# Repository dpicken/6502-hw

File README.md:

# 6502-hw

Schematics and PCBs for a [Ben Eater](https://eater.net/6502) inspired 6502 computer.

## SBC

The single board computer ([schematic](/pdf/sbc.pdf), [layout](pdf/sbc.pcb.pdf), [BOM](bom/sbc.md)), features include:

  - 65C02 CPU, 8 MHz (with a suitable EEPROM)
  - ATF22V10C PLD (address space decode and IRQ glue)
  - 32 KiB ROM
  - 32 KiB RAM
  - 32 GiB microSD mass storage
  - 3 VIAs (1 system, 2 user accessible)
  - USB serial

### Programmable Logic

Install [rust](https://www.rust-lang.org/tools/install), then install galette:

```
git clone https://github.com/simon-frankau/galette
bash -c "cd galette; cargo build --release"
cp galette/target/release/galette ~/bin
```

Clone the fab build system and the 6502-hw project:

```
git clone https://github.com/dpicken/fab
git clone https://github.com/dpicken/6502-hw
```

Build:

```
cd 6502-hw
make
```

Write ATF22v10C:

```
make install
```

### Software

- See [dpicken/6502-os](https://github.com/dpicken/6502-os).

## SBC Controller

A controller for the single board computer ([schematic](/pdf/sbc-exp-control.pdf), [layout](pdf/sbc-exp-control.pcb.pdf), [BOM](bom/sbc-exp-control.md)).

## SBC Display - 20x4 OLED character module

An OLED display for the single board computer ([schematic](/pdf/sbc-exp-nhd_0420cw-interposer.pdf), [layout](pdf/sbc-exp-nhd_0420cw-interposer.pcb.pdf), [BOM](bom/sbc-exp-nhd_0420cw-interposer.md)).

## SBC Display - 40x4 or 20x4 LCD character module

An LCD display for the single board computer ([schematic](/pdf/sbc-exp-erm4004_erm2004-interposer.pdf), [layout](pdf/sbc-exp-erm4004_erm2004-interposer.pcb.pdf), [BOM](bom/sbc-exp-erm4004_erm2004-interposer.md)).

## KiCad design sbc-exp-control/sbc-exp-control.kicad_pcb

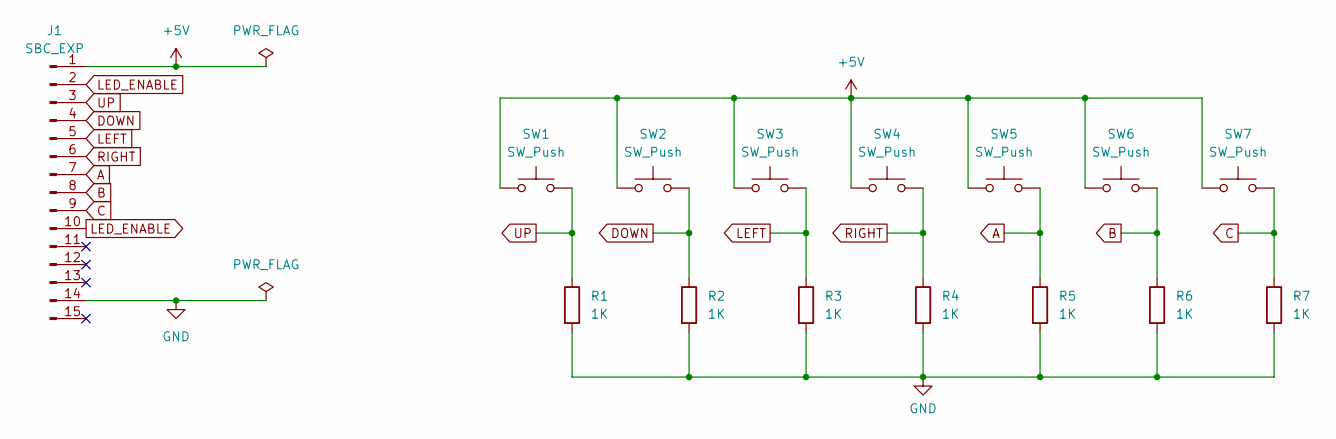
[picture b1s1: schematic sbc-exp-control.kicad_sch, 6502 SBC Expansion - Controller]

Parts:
J1: SBC_EXP; PinHeader_1x15_P2.54mm_Vertical
R1, R2, R3, R4, R5, R6, R7: 1K; R_0805_2012Metric_Pad1.20x1.40mm_HandSolder
SW1, SW2, SW3, SW4, SW5, SW6, SW7: SW_Push; SW_Push_1P1T_NO_6x6mm_H9.5mm

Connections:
+5V: J1.1, SW1.1, SW2.1, SW3.1, SW4.1, SW5.1, SW6.1, SW7.1
A: J1.7, R5.1, SW5.2
B: J1.8, R6.1, SW6.2
C: J1.9, R7.1, SW7.2
DOWN: J1.4, R2.1, SW2.2
GND: J1.14, R1.2, R2.2, R3.2, R4.2, R5.2, R6.2, R7.2
LED_ENABLE: J1.2, J1.10
LEFT: J1.5, R3.1, SW3.2
RIGHT: J1.6, R4.1, SW4.2
UP: J1.3, R1.1, SW1.2

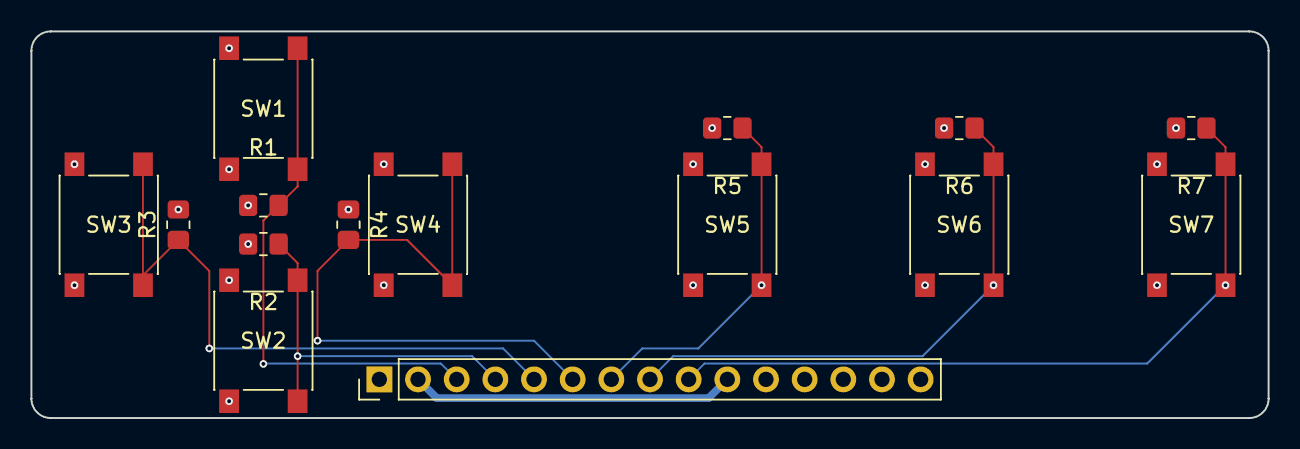
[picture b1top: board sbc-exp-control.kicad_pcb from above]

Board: 4 copper layers, 81.3 x 25.4 mm, 15 parts (0 on the bottom side), 10 nets.

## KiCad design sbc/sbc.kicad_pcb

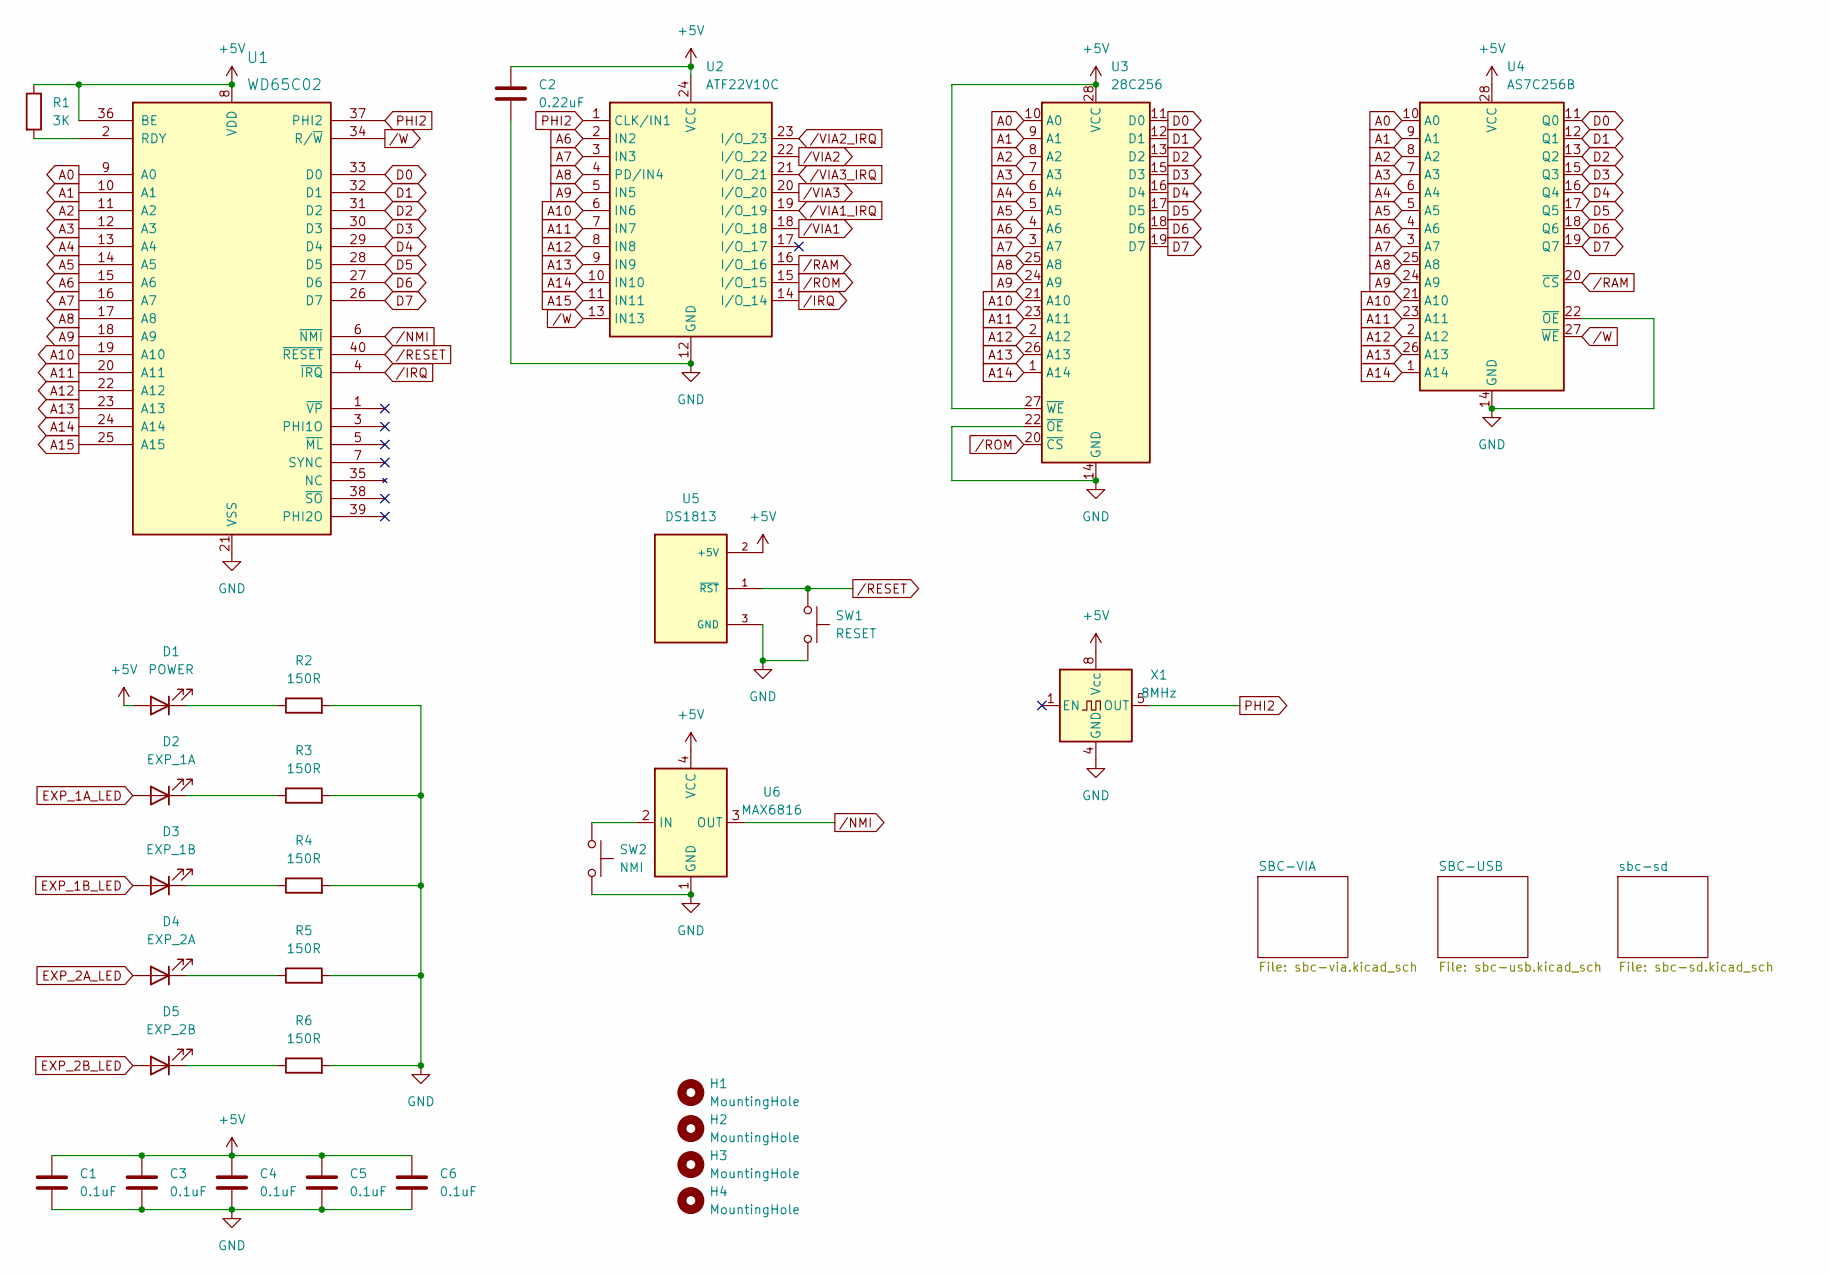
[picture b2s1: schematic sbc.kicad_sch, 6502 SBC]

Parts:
C1, C3, C4, C5, C6: 0.1uF; C_0805_2012Metric_Pad1.18x1.45mm_HandSolder
C2: 0.22uF; C_0805_2012Metric_Pad1.18x1.45mm_HandSolder
D1: POWER; LED_Rectangular_W5.0mm_H2.0mm
D2: EXP_1A; LED_Rectangular_W5.0mm_H2.0mm
D3: EXP_1B; LED_Rectangular_W5.0mm_H2.0mm
D4: EXP_2A; LED_Rectangular_W5.0mm_H2.0mm
D5: EXP_2B; LED_Rectangular_W5.0mm_H2.0mm
H1, H2, H3, H4: MountingHole; MountingHole_2.2mm_M2_Pad
R1: 3K; R_0805_2012Metric_Pad1.20x1.40mm_HandSolder
R2, R3, R4, R5, R6: 150R; R_0805_2012Metric_Pad1.20x1.40mm_HandSolder
SW1: RESET; SW_PUSH_6mm_H4.3mm
SW2: NMI; SW_PUSH_6mm_H4.3mm
U1: WD65C02; DIP-40_W15.24mm_Socket
U2: ATF22V10C; DIP-24_W7.62mm_Socket
U3: 28C256; DIP-28_W15.24mm_Socket
U4: AS7C256B; DIP-28_W7.62mm_Socket
U5: DS1813; SOT-23_Handsoldering
U6: MAX6816; SOT-143_Handsoldering
X1: 8MHz; Oscillator_DIP-8

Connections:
+5V: C1.1, C2.1, C3.1, C4.1, C5.1, C6.1, D1.2 (A), R1.1, U1.8 (VDD), U1.36 (BE), U2.24 (VCC), U3.27 (~WE), U3.28 (VCC), U4.28 (VCC), U5.2 (+5V), U6.4 (VCC), X1.8 (Vcc); also elsewhere on the board
A0: U1.9 (A0), U3.10 (A0), U4.10 (A0); also elsewhere on the board
A1: U1.10 (A1), U3.9 (A1), U4.9 (A1); also elsewhere on the board
A2: U1.11 (A2), U3.8 (A2), U4.8 (A2); also elsewhere on the board
A3: U1.12 (A3), U3.7 (A3), U4.7 (A3); also elsewhere on the board
A4: U1.13 (A4), U3.6 (A4), U4.6 (A4)
A5: U1.14 (A5), U3.5 (A5), U4.5 (A5)
A6: U1.15 (A6), U2.2 (IN2), U3.4 (A6), U4.4 (A6)
A7: U1.16 (A7), U2.3 (IN3), U3.3 (A7), U4.3 (A7)
A8: U1.17 (A8), U2.4 (PD/IN4), U3.25 (A8), U4.25 (A8)
A9: U1.18 (A9), U2.5 (IN5), U3.24 (A9), U4.24 (A9)
A10: U1.19 (A10), U2.6 (IN6), U3.21 (A10), U4.21 (A10)
A11: U1.20 (A11), U2.7 (IN7), U3.23 (A11), U4.23 (A11)
A12: U1.22 (A12), U2.8 (IN8), U3.2 (A12), U4.2 (A12)
A13: U1.23 (A13), U2.9 (IN9), U3.26 (A13), U4.26 (A13)
A14: U1.24 (A14), U2.10 (IN10), U3.1 (A14), U4.1 (A14)
A15: U1.25 (A15), U2.11 (IN11)
D0: U1.33 (D0), U3.11 (D0), U4.11 (Q0); also elsewhere on the board
D1: U1.32 (D1), U3.12 (D1), U4.12 (Q1); also elsewhere on the board
D2: U1.31 (D2), U3.13 (D2), U4.13 (Q2); also elsewhere on the board
D3: U1.30 (D3), U3.15 (D3), U4.15 (Q3); also elsewhere on the board
D4: U1.29 (D4), U3.16 (D4), U4.16 (Q4); also elsewhere on the board
D5: U1.28 (D5), U3.17 (D5), U4.17 (Q5); also elsewhere on the board
D6: U1.27 (D6), U3.18 (D6), U4.18 (Q6); also elsewhere on the board
D7: U1.26 (D7), U3.19 (D7), U4.19 (Q7); also elsewhere on the board
EXP_1A_LED: D2.2 (A); also elsewhere on the board
EXP_1B_LED: D3.2 (A); also elsewhere on the board
EXP_2A_LED: D4.2 (A); also elsewhere on the board
EXP_2B_LED: D5.2 (A); also elsewhere on the board
GND: C1.2, C2.2, C3.2, C4.2, C5.2, C6.2, R2.2, R3.2, R4.2, R5.2, R6.2, SW1.2, SW2.2, U1.21 (VSS), U2.12 (GND), U3.14 (GND), U3.22 (~OE), U4.14 (GND), U4.22 (~OE), U5.3 (GND), U6.1 (GND), X1.4 (GND); also elsewhere on the board
unnamed: D1.1 (K), R2.1
unnamed: D2.1 (K), R3.1
unnamed: D3.1 (K), R4.1
unnamed: D4.1 (K), R5.1
unnamed: D5.1 (K), R6.1
unnamed: R1.2, U1.2 (RDY)
unnamed: SW2.1, U6.2 (IN)
PHI2: U1.37 (PHI2), U2.1 (CLK/IN1), X1.5 (OUT); also elsewhere on the board
/IRQ: U1.4 (~IRQ), U2.14 (I/O_14)
/NMI: U1.6 (~NMI), U6.3 (OUT)
/RAM: U2.16 (I/O_16), U4.20 (~CS)
/RESET: SW1.1, U1.40 (~RESET), U5.1 (~RST); also elsewhere on the board
/ROM: U2.15 (I/O_15), U3.20 (~CS)
/VIA1: U2.18 (I/O_18); also elsewhere on the board
/VIA1_IRQ: U2.19 (I/O_19); also elsewhere on the board
/VIA2: U2.22 (I/O_22); also elsewhere on the board
/VIA2_IRQ: U2.23 (I/O_23); also elsewhere on the board
/VIA3: U2.20 (I/O_20); also elsewhere on the board
/VIA3_IRQ: U2.21 (I/O_21); also elsewhere on the board
/W: U1.34 (R/~W), U2.13 (IN13), U4.27 (~WE); also elsewhere on the board

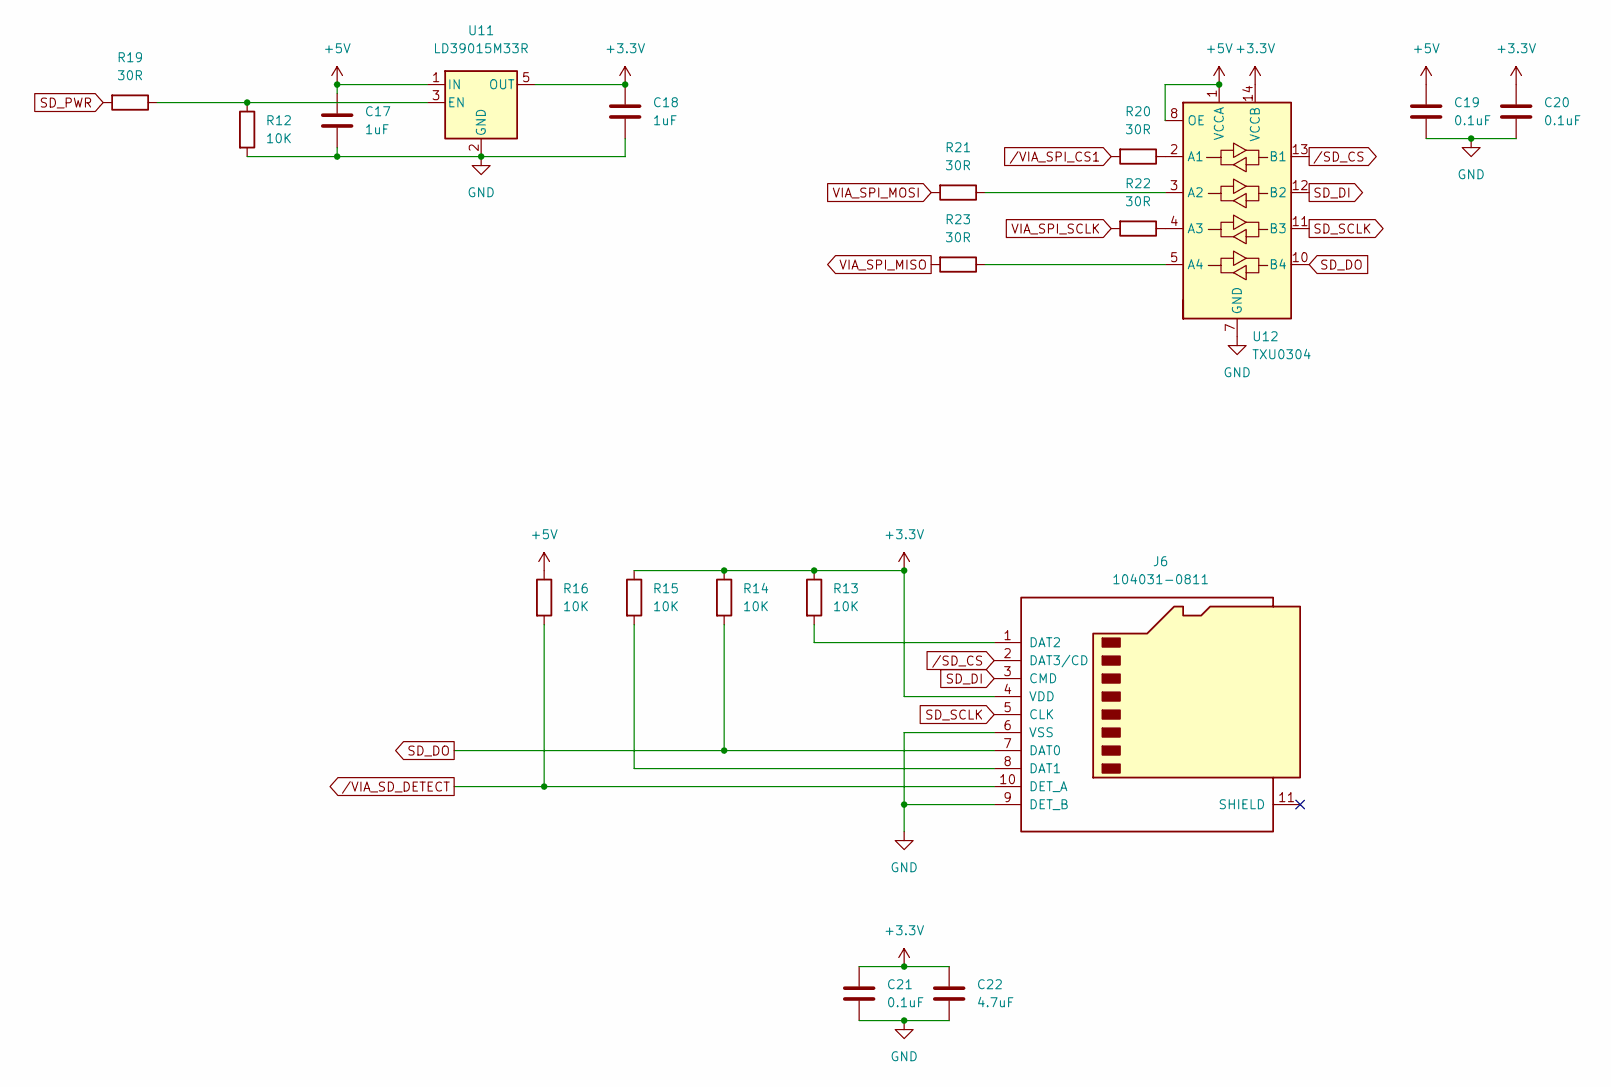
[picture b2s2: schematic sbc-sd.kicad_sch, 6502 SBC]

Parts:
C17, C18: 1uF; C_0805_2012Metric_Pad1.18x1.45mm_HandSolder
C19, C20, C21: 0.1uF; C_0805_2012Metric_Pad1.18x1.45mm_HandSolder
C22: 4.7uF; C_0805_2012Metric_Pad1.18x1.45mm_HandSolder
J6: 104031-0811; microSD_HC_Molex_104031-0811_HandSoler
R12, R13, R14, R15, R16: 10K; R_0805_2012Metric_Pad1.20x1.40mm_HandSolder
R19, R20, R21, R22, R23: 30R; R_0805_2012Metric_Pad1.20x1.40mm_HandSolder
U11: LD39015M33R; SOT-23-5_HandSoldering
U12: TXU0304; TSSOP-14_4.4x5mm_P0.65mm

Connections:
+3V3: C18.1, C20.1, C21.1, C22.1, J6.4 (VDD), R13.1, R14.1, R15.1, U11.5 (OUT), U12.14 (VCCB)
+5V: C17.1, C19.1, R16.1, U11.1 (IN), U12.1 (VCCA), U12.8 (OE); also elsewhere on the board
GND: C17.2, C18.2, C19.2, C20.2, C21.2, C22.2, J6.6 (VSS), J6.9 (DET_B), R12.2, U11.2 (GND), U12.7 (GND); also elsewhere on the board
unnamed: J6.1 (DAT2), R13.2
unnamed: J6.8 (DAT1), R15.2
unnamed: R12.1, R19.1, U11.3 (EN)
unnamed: R20.1, U12.2 (A1)
unnamed: R21.1, U12.3 (A2)
unnamed: R22.1, U12.4 (A3)
unnamed: R23.1, U12.5 (A4)
SD_DI: J6.3 (CMD), U12.12 (B2)
SD_DO: J6.7 (DAT0), R14.2, U12.10 (B4)
SD_PWR: R19.2; also elsewhere on the board
SD_SCLK: J6.5 (CLK), U12.11 (B3)
VIA_SPI_MISO: R23.2; also elsewhere on the board
VIA_SPI_MOSI: R21.2; also elsewhere on the board
VIA_SPI_SCLK: R22.2; also elsewhere on the board
/SD_CS: J6.2 (DAT3/CD), U12.13 (B1)
/VIA_SD_DETECT: J6.10 (DET_A), R16.2; also elsewhere on the board
/VIA_SPI_CS1: R20.2; also elsewhere on the board

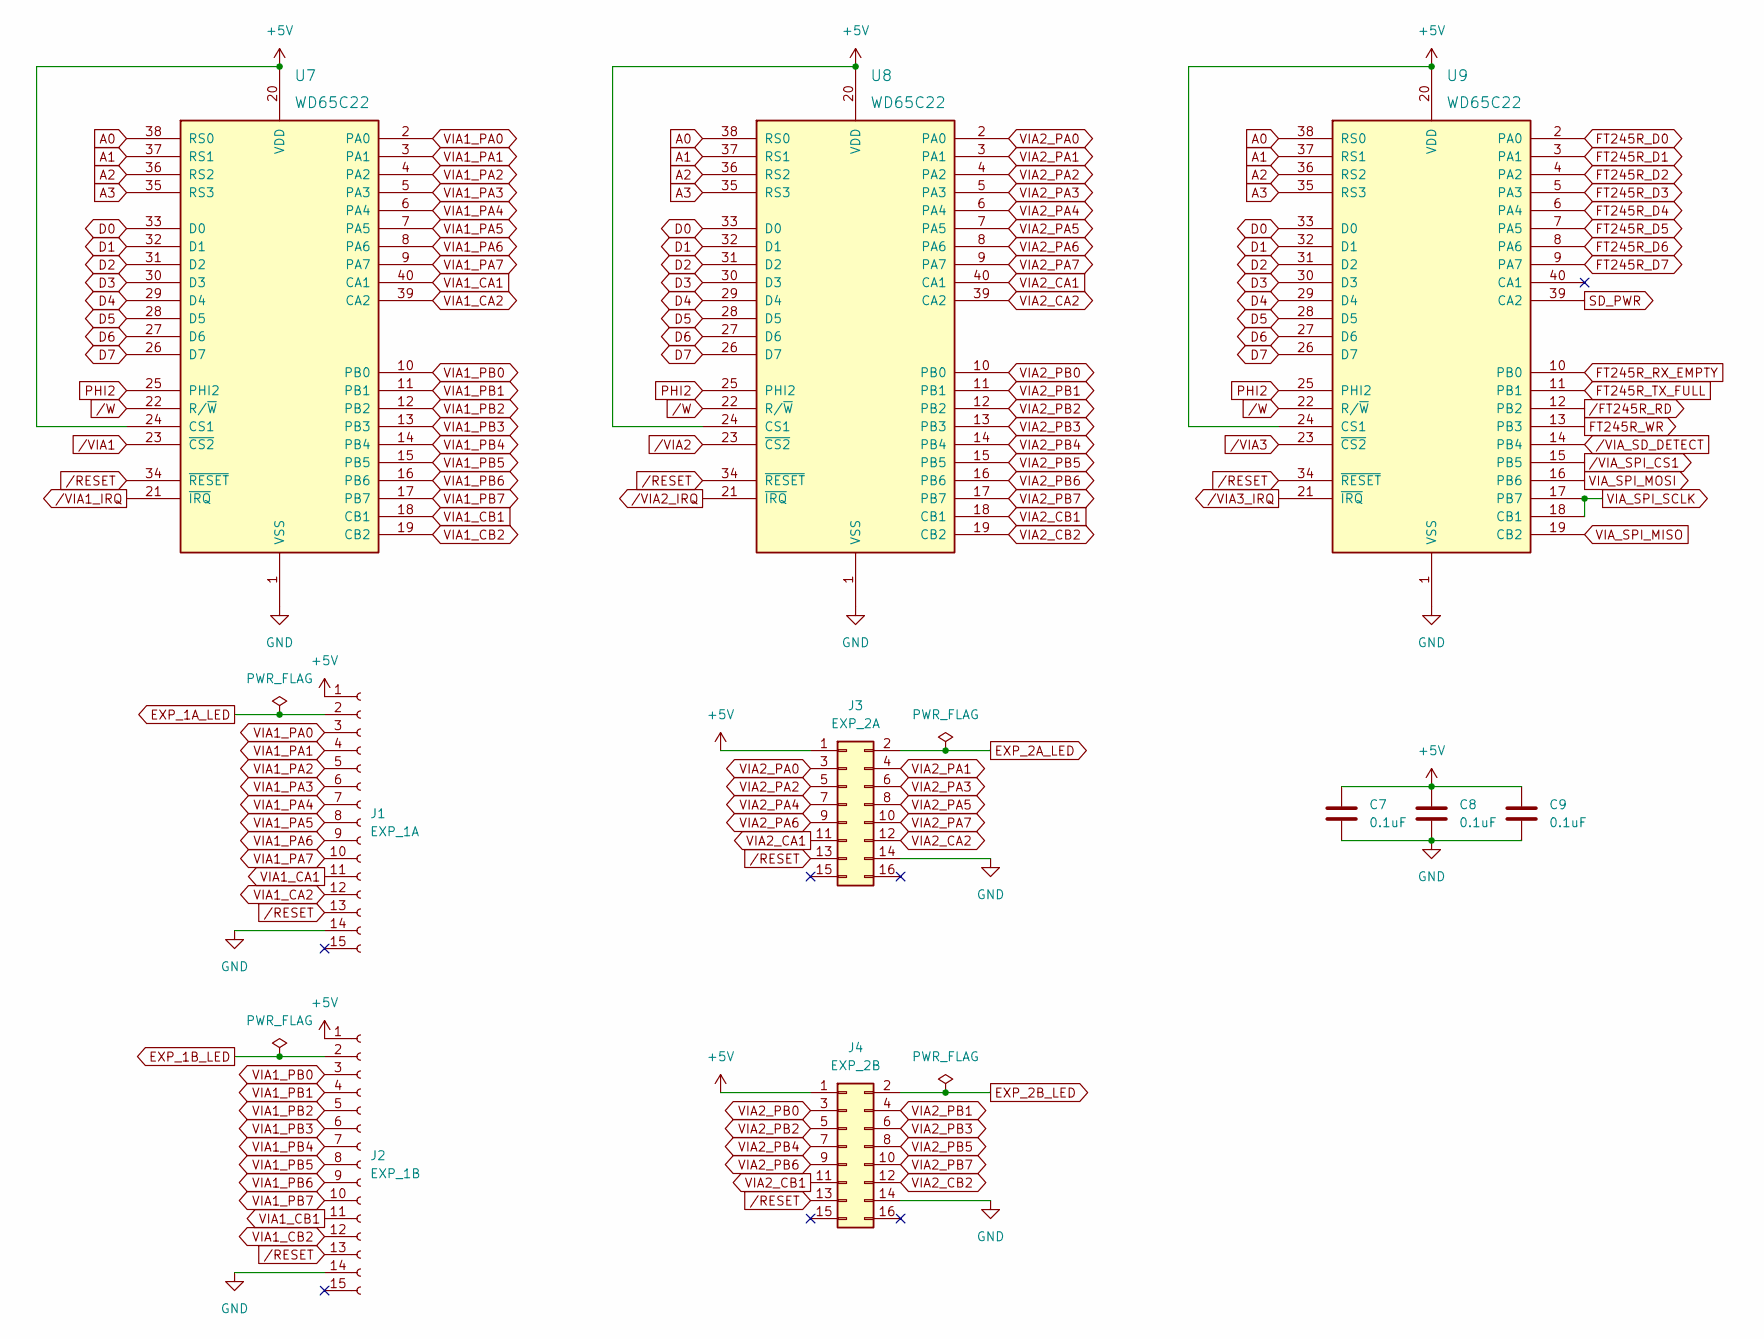
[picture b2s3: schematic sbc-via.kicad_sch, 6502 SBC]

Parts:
C7, C8, C9: 0.1uF; C_0805_2012Metric_Pad1.18x1.45mm_HandSolder
J1: EXP_1A; PinSocket_1x15_P2.54mm_Vertical
J2: EXP_1B; PinSocket_1x15_P2.54mm_Vertical
J3: EXP_2A; PinHeader_2x08_P2.54mm_Vertical
J4: EXP_2B; PinHeader_2x08_P2.54mm_Vertical
U7, U8, U9: WD65C22; DIP-40_W15.24mm_Socket

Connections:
+5V: C7.1, C8.1, C9.1, J1.1, J2.1, J3.1, J4.1, U7.20 (VDD), U7.24 (CS1), U8.20 (VDD), U8.24 (CS1), U9.20 (VDD), U9.24 (CS1); also elsewhere on the board
A0: U7.38 (RS0), U8.38 (RS0), U9.38 (RS0); also elsewhere on the board
A1: U7.37 (RS1), U8.37 (RS1), U9.37 (RS1); also elsewhere on the board
A2: U7.36 (RS2), U8.36 (RS2), U9.36 (RS2); also elsewhere on the board
A3: U7.35 (RS3), U8.35 (RS3), U9.35 (RS3); also elsewhere on the board
D0: U7.33 (D0), U8.33 (D0), U9.33 (D0); also elsewhere on the board
D1: U7.32 (D1), U8.32 (D1), U9.32 (D1); also elsewhere on the board
D2: U7.31 (D2), U8.31 (D2), U9.31 (D2); also elsewhere on the board
D3: U7.30 (D3), U8.30 (D3), U9.30 (D3); also elsewhere on the board
D4: U7.29 (D4), U8.29 (D4), U9.29 (D4); also elsewhere on the board
D5: U7.28 (D5), U8.28 (D5), U9.28 (D5); also elsewhere on the board
D6: U7.27 (D6), U8.27 (D6), U9.27 (D6); also elsewhere on the board
D7: U7.26 (D7), U8.26 (D7), U9.26 (D7); also elsewhere on the board
EXP_1A_LED: J1.2; also elsewhere on the board
EXP_1B_LED: J2.2; also elsewhere on the board
EXP_2A_LED: J3.2; also elsewhere on the board
EXP_2B_LED: J4.2; also elsewhere on the board
FT245R_D0: U9.2 (PA0); also elsewhere on the board
FT245R_D1: U9.3 (PA1); also elsewhere on the board
FT245R_D2: U9.4 (PA2); also elsewhere on the board
FT245R_D3: U9.5 (PA3); also elsewhere on the board
FT245R_D4: U9.6 (PA4); also elsewhere on the board
FT245R_D5: U9.7 (PA5); also elsewhere on the board
FT245R_D6: U9.8 (PA6); also elsewhere on the board
FT245R_D7: U9.9 (PA7); also elsewhere on the board
FT245R_RX_EMPTY: U9.10 (PB0); also elsewhere on the board
FT245R_TX_FULL: U9.11 (PB1); also elsewhere on the board
FT245R_WR: U9.13 (PB3); also elsewhere on the board
GND: C7.2, C8.2, C9.2, J1.14, J2.14, J3.14, J4.14, U7.1 (VSS), U8.1 (VSS), U9.1 (VSS); also elsewhere on the board
PHI2: U7.25 (PHI2), U8.25 (PHI2), U9.25 (PHI2); also elsewhere on the board
SD_PWR: U9.39 (CA2); also elsewhere on the board
VIA1_CA1: J1.11, U7.40 (CA1)
VIA1_CA2: J1.12, U7.39 (CA2)
VIA1_CB1: J2.11, U7.18 (CB1)
VIA1_CB2: J2.12, U7.19 (CB2)
VIA1_PA0: J1.3, U7.2 (PA0)
VIA1_PA1: J1.4, U7.3 (PA1)
VIA1_PA2: J1.5, U7.4 (PA2)
VIA1_PA3: J1.6, U7.5 (PA3)
VIA1_PA4: J1.7, U7.6 (PA4)
VIA1_PA5: J1.8, U7.7 (PA5)
VIA1_PA6: J1.9, U7.8 (PA6)
VIA1_PA7: J1.10, U7.9 (PA7)
VIA1_PB0: J2.3, U7.10 (PB0)
VIA1_PB1: J2.4, U7.11 (PB1)
VIA1_PB2: J2.5, U7.12 (PB2)
VIA1_PB3: J2.6, U7.13 (PB3)
VIA1_PB4: J2.7, U7.14 (PB4)
VIA1_PB5: J2.8, U7.15 (PB5)
VIA1_PB6: J2.9, U7.16 (PB6)
VIA1_PB7: J2.10, U7.17 (PB7)
VIA2_CA1: J3.11, U8.40 (CA1)
VIA2_CA2: J3.12, U8.39 (CA2)
VIA2_CB1: J4.11, U8.18 (CB1)
VIA2_CB2: J4.12, U8.19 (CB2)
VIA2_PA0: J3.3, U8.2 (PA0)
VIA2_PA1: J3.4, U8.3 (PA1)
VIA2_PA2: J3.5, U8.4 (PA2)
VIA2_PA3: J3.6, U8.5 (PA3)
VIA2_PA4: J3.7, U8.6 (PA4)
VIA2_PA5: J3.8, U8.7 (PA5)
VIA2_PA6: J3.9, U8.8 (PA6)
VIA2_PA7: J3.10, U8.9 (PA7)
VIA2_PB0: J4.3, U8.10 (PB0)
VIA2_PB1: J4.4, U8.11 (PB1)
VIA2_PB2: J4.5, U8.12 (PB2)
VIA2_PB3: J4.6, U8.13 (PB3)
VIA2_PB4: J4.7, U8.14 (PB4)
VIA2_PB5: J4.8, U8.15 (PB5)
VIA2_PB6: J4.9, U8.16 (PB6)
VIA2_PB7: J4.10, U8.17 (PB7)
VIA_SPI_MISO: U9.19 (CB2); also elsewhere on the board
VIA_SPI_MOSI: U9.16 (PB6); also elsewhere on the board
VIA_SPI_SCLK: U9.17 (PB7), U9.18 (CB1); also elsewhere on the board
/FT245R_RD: U9.12 (PB2); also elsewhere on the board
/RESET: J1.13, J2.13, J3.13, J4.13, U7.34 (~RESET), U8.34 (~RESET), U9.34 (~RESET); also elsewhere on the board
/VIA1: U7.23 (~CS2); also elsewhere on the board
/VIA1_IRQ: U7.21 (~IRQ); also elsewhere on the board
/VIA2: U8.23 (~CS2); also elsewhere on the board
/VIA2_IRQ: U8.21 (~IRQ); also elsewhere on the board
/VIA3: U9.23 (~CS2); also elsewhere on the board
/VIA3_IRQ: U9.21 (~IRQ); also elsewhere on the board
/VIA_SD_DETECT: U9.14 (PB4); also elsewhere on the board
/VIA_SPI_CS1: U9.15 (PB5); also elsewhere on the board
/W: U7.22 (R/~W), U8.22 (R/~W), U9.22 (R/~W); also elsewhere on the board

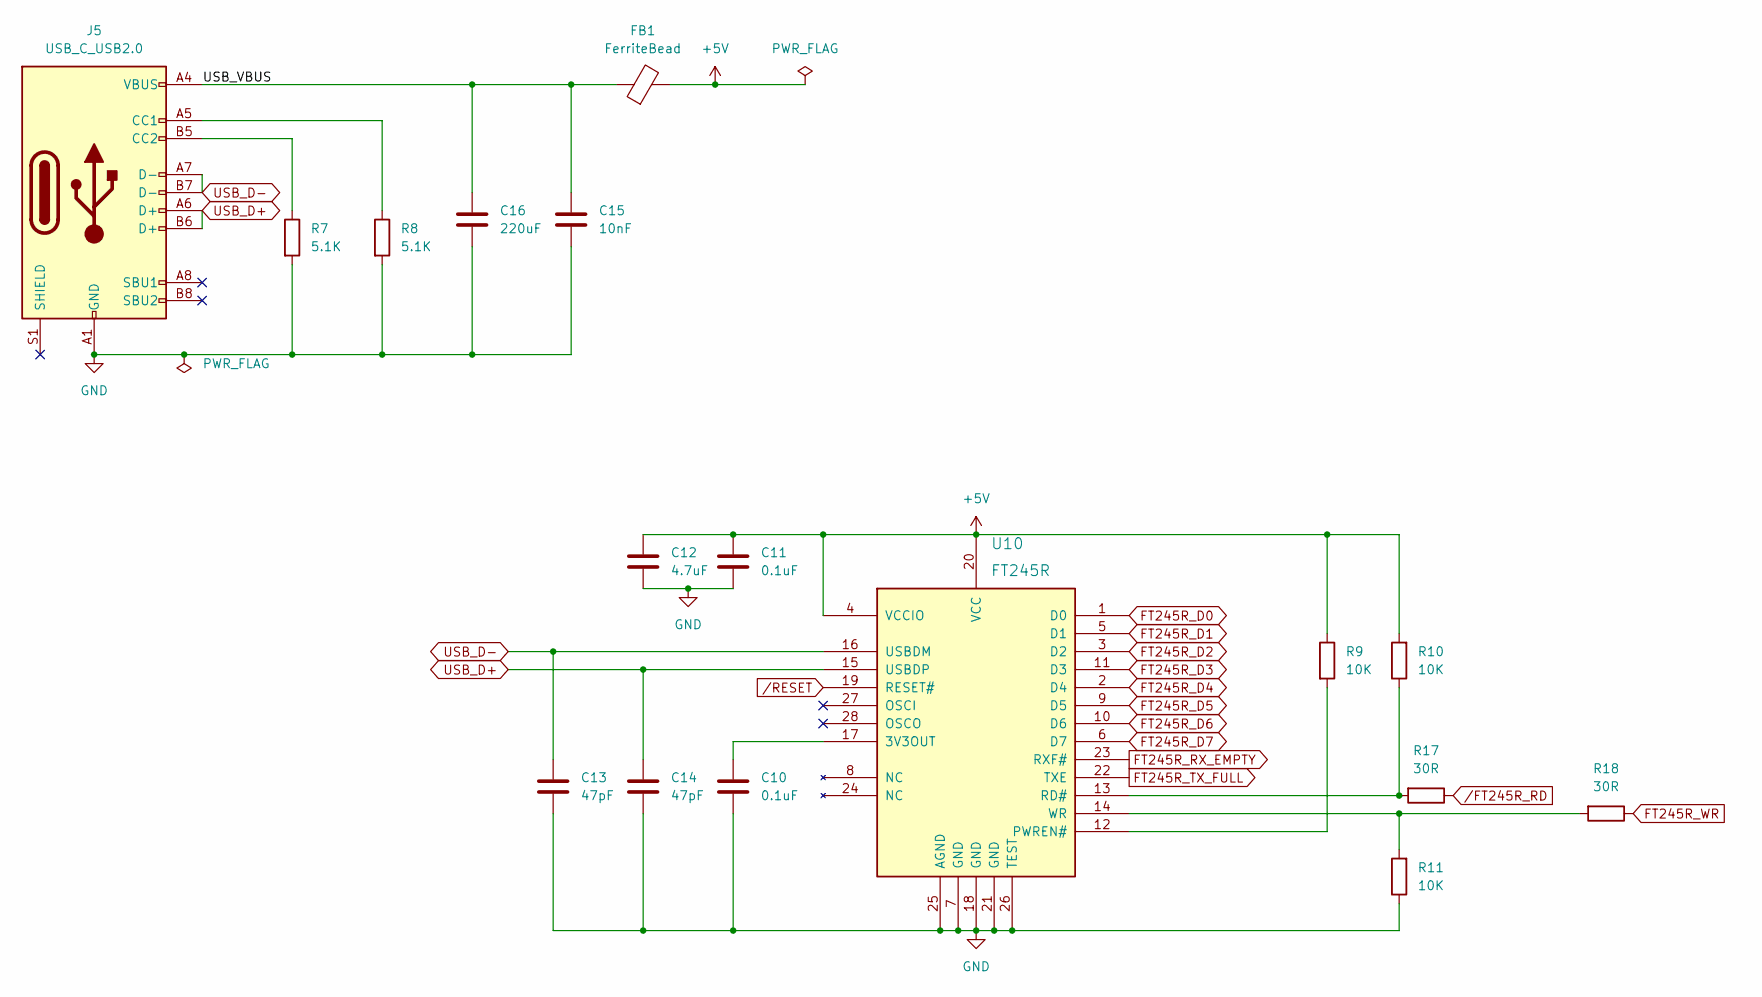
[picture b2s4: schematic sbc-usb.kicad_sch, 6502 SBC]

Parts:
C10, C11: 0.1uF; C_0805_2012Metric_Pad1.18x1.45mm_HandSolder
C12: 4.7uF; C_0805_2012Metric_Pad1.18x1.45mm_HandSolder
C13, C14: 47pF; C_0805_2012Metric_Pad1.18x1.45mm_HandSolder
C15: 10nF; C_0805_2012Metric_Pad1.18x1.45mm_HandSolder
C16: 220uF; CP_Radial_D6.3mm_P2.50mm
FB1: FerriteBead; R_0805_2012Metric_Pad1.20x1.40mm_HandSolder
J5: USB_C_USB2.0; USB_C_Receptacle_GCT_USB4085
R7, R8: 5.1K; R_0805_2012Metric_Pad1.20x1.40mm_HandSolder
R9, R10, R11: 10K; R_0805_2012Metric_Pad1.20x1.40mm_HandSolder
R17, R18: 30R; R_0805_2012Metric_Pad1.20x1.40mm_HandSolder
U10: FT245R; SSOP-28_5.3x10.2mm_P0.65mm

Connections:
+5V: C11.1, C12.1, FB1.2, R9.1, R10.2, U10.4 (VCCIO), U10.20 (VCC); also elsewhere on the board
/SBC-USB/USB_VBUS: C15.1, C16.1, FB1.1, J5.A4 (VBUS), J5.A9 (VBUS), J5.B4 (VBUS), J5.B9 (VBUS)
FT245R_D0: U10.1 (D0); also elsewhere on the board
FT245R_D1: U10.5 (D1); also elsewhere on the board
FT245R_D2: U10.3 (D2); also elsewhere on the board
FT245R_D3: U10.11 (D3); also elsewhere on the board
FT245R_D4: U10.2 (D4); also elsewhere on the board
FT245R_D5: U10.9 (D5); also elsewhere on the board
FT245R_D6: U10.10 (D6); also elsewhere on the board
FT245R_D7: U10.6 (D7); also elsewhere on the board
FT245R_RX_EMPTY: U10.23 (RXF#); also elsewhere on the board
FT245R_TX_FULL: U10.22 (TXE); also elsewhere on the board
FT245R_WR: R18.1; also elsewhere on the board
GND: C10.2, C11.2, C12.2, C13.2, C14.2, C15.2, C16.2, J5.A1 (GND), J5.A12 (GND), J5.B1 (GND), J5.B12 (GND), R7.2, R8.2, R11.1, U10.7 (GND), U10.18 (GND), U10.21 (GND), U10.25 (AGND), U10.26 (TEST); also elsewhere on the board
unnamed: C10.1, U10.17 (3V3OUT)
unnamed: J5.A5 (CC1), R8.1
unnamed: J5.B5 (CC2), R7.1
unnamed: R9.2, U10.12 (PWREN#)
unnamed: R10.1, R17.2, U10.13 (RD#)
unnamed: R11.2, R18.2, U10.14 (WR)
USB_D+: C14.1, J5.A6 (D+), J5.B6 (D+), U10.15 (USBDP)
USB_D-: C13.1, J5.A7 (D-), J5.B7 (D-), U10.16 (USBDM)
/FT245R_RD: R17.1; also elsewhere on the board
/RESET: U10.19 (RESET#); also elsewhere on the board

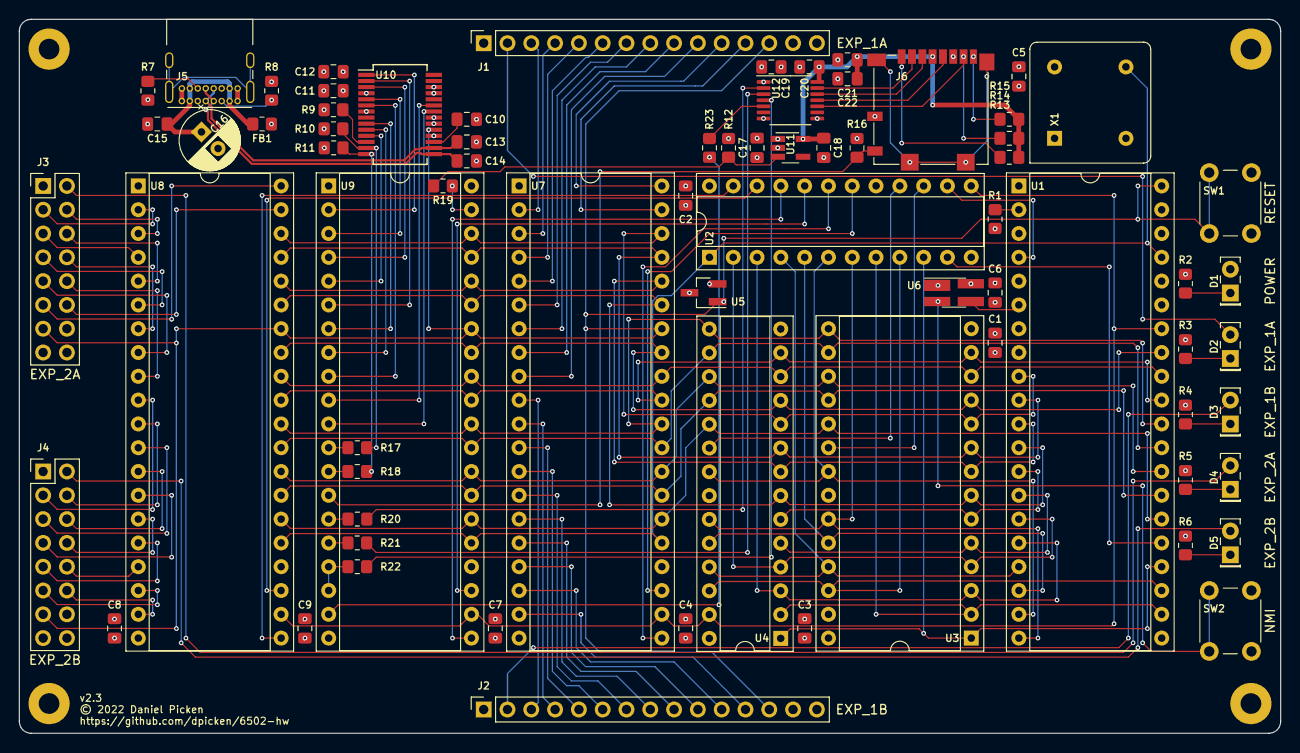
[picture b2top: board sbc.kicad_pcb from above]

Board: 4 copper layers, 134.6 x 76.2 mm, 76 parts (0 on the bottom side), 129 nets.

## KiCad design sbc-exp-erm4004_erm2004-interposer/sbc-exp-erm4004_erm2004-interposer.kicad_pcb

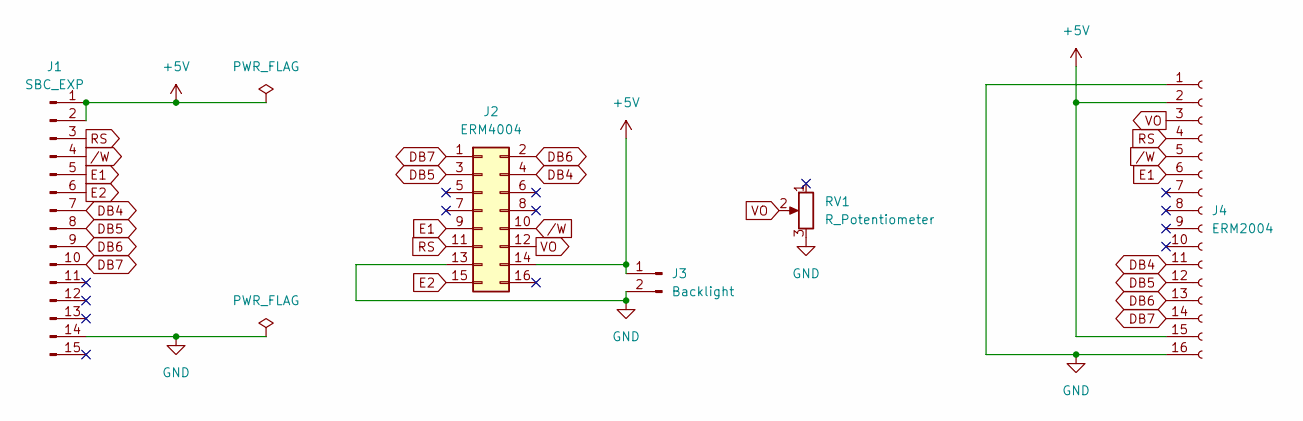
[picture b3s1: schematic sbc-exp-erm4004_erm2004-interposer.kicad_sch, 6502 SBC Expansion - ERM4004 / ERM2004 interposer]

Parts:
J1: SBC_EXP; PinHeader_1x15_P2.54mm_Vertical
J2: ERM4004; IDC-Header_2x08_P2.54mm_Vertical
J3: Backlight; PinHeader_1x02_P2.54mm_Horizontal
J4: ERM2004; PinSocket_1x16_P2.54mm_Vertical
RV1: R_Potentiometer; Potentiometer_Vishay_T73XW_Horizontal

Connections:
+5V: J1.1, J1.2, J2.14, J3.1, J4.2, J4.15
DB4: J1.7, J2.4, J4.11
DB5: J1.8, J2.3, J4.12
DB6: J1.9, J2.2, J4.13
DB7: J1.10, J2.1, J4.14
E1: J1.5, J2.9, J4.6
E2: J1.6, J2.15
GND: J1.14, J2.13, J3.2, J4.1, J4.16, RV1.3
RS: J1.3, J2.11, J4.4
VO: J2.12, J4.3, RV1.2
/W: J1.4, J2.10, J4.5

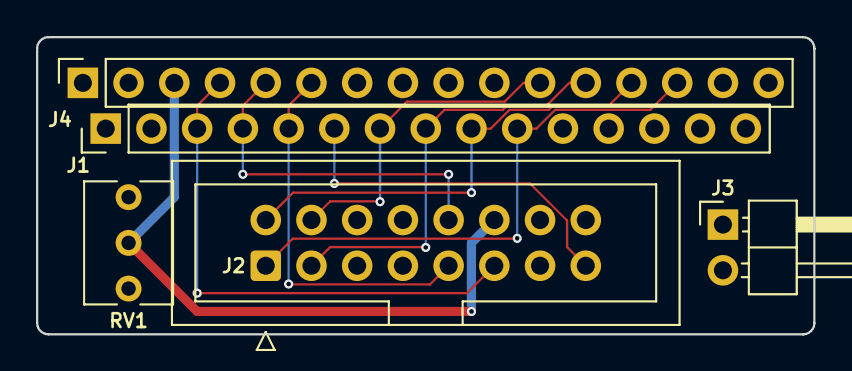
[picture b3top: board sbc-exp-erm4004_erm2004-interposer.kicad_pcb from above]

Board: 4 copper layers, 43.2 x 16.5 mm, 5 parts (0 on the bottom side), 11 nets.

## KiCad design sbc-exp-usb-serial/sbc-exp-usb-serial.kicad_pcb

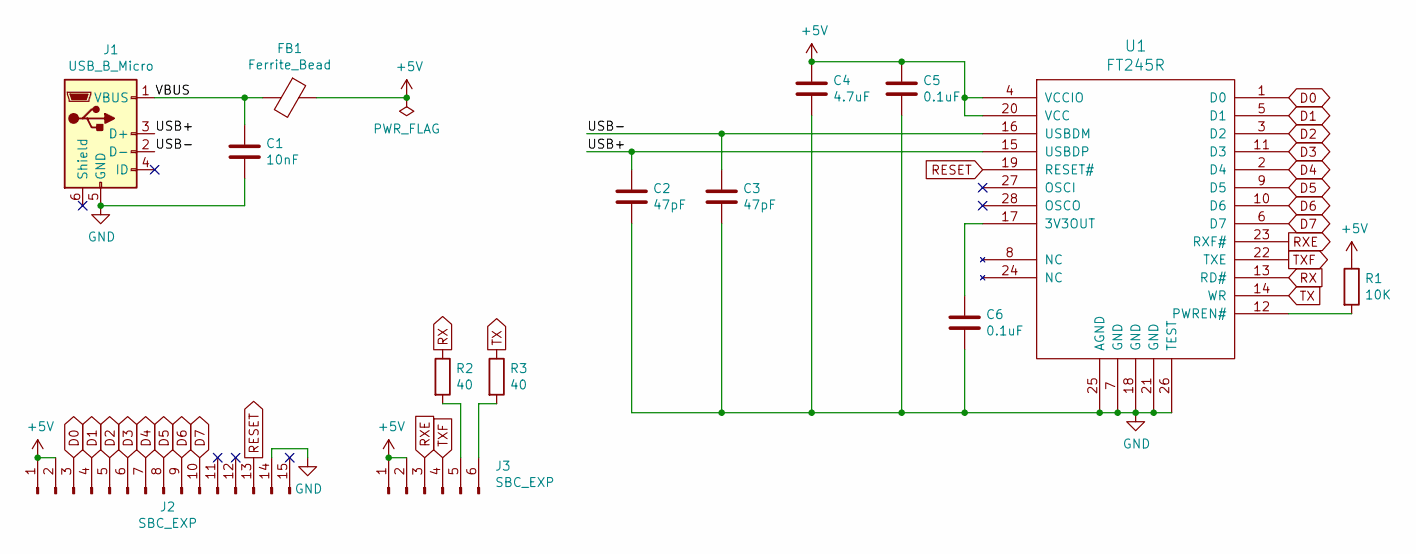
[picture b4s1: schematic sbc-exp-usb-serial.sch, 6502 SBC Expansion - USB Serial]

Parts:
C1: 10nF; C_Disc_D5.0mm_W2.5mm_P2.50mm
C2, C3: 47pF; C_Disc_D5.0mm_W2.5mm_P2.50mm
C4: 4.7uF; C_Disc_D5.0mm_W2.5mm_P2.50mm
C5, C6: 0.1uF; C_Disc_D5.0mm_W2.5mm_P2.50mm
FB1: Ferrite_Bead; R_0805_2012Metric_Pad1.20x1.40mm_HandSolder
J1: USB_B_Micro; USB_Micro-B_Amphenol_10118194_Horizontal_HandSoldering
J2: SBC_EXP; PinHeader_1x15_P2.54mm_Vertical
J3: SBC_EXP; PinHeader_1x06_P2.54mm_Vertical
R1: 10K; R_Axial_DIN0204_L3.6mm_D1.6mm_P5.08mm_Horizontal
R2, R3: 40; R_Axial_DIN0204_L3.6mm_D1.6mm_P5.08mm_Horizontal
U1: FT245R; SSOP-28_5.3x10.2mm_P0.65mm

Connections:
+5V: C4.1, C5.1, FB1.1, J2.1, J2.2, J3.1, J3.2, R1.1, U1.4 (VCCIO), U1.20 (VCC)
/USB+: C2.1, J1.3 (D+), U1.15 (USBDP)
/USB-: C3.1, J1.2 (D-), U1.16 (USBDM)
/VBUS: C1.1, FB1.2, J1.1 (VBUS)
D0: J2.3, U1.1 (D0)
D1: J2.4, U1.5 (D1)
D2: J2.5, U1.3 (D2)
D3: J2.6, U1.11 (D3)
D4: J2.7, U1.2 (D4)
D5: J2.8, U1.9 (D5)
D6: J2.9, U1.10 (D6)
D7: J2.10, U1.6 (D7)
GND: C1.2, C2.2, C3.2, C4.2, C5.2, C6.1, J1.5 (GND), J2.14, U1.7 (GND), U1.18 (GND), U1.21 (GND), U1.25 (AGND), U1.26 (TEST)
unnamed: C6.2, U1.17 (3V3OUT)
unnamed: J3.5, R2.2
unnamed: J3.6, R3.2
unnamed: R1.2, U1.12 (PWREN#)
RESET: J2.13, U1.19 (RESET#)
RX: R2.1, U1.13 (RD#)
RXE: J3.3, U1.23 (RXF#)
TX: R3.1, U1.14 (WR)
TXF: J3.4, U1.22 (TXE)

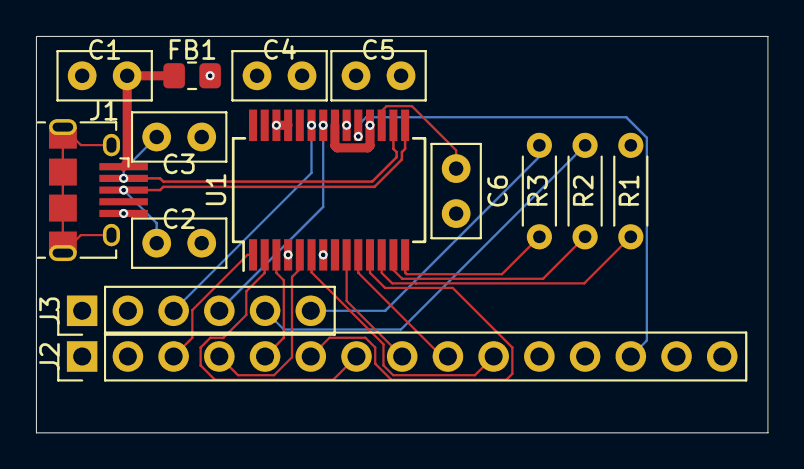
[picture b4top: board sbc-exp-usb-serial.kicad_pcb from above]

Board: 4 copper layers, 40.6 x 22.0 mm, 14 parts (0 on the bottom side), 22 nets.

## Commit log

2021-07-29 Add kicad and 65xx chipset symbols
2021-07-30 Add SBC project and configure its libraries
2021-08-03 SBC: Wire up data and address buses
2021-08-03 SBC: Wire up glue logic
2021-08-03 SBC: Wire up power
2021-08-03 SBC: Wire up peripheral A and B connectors
2021-08-04 SBC: Wire up oscillator
2021-08-20 SBC: Power and reset
2021-09-01 SBC: Assign footprints
2021-09-03 SBC: Configure OHSPark design rules and start layout
2021-09-10 SBC: Wire up memories
2021-09-10 SBC: Wire up signals
2021-09-10 SBC: Wire up power and ground
2021-09-10 SBC: Add mounting holes and polish silkscreen
2021-09-10 SBC: Add board outline
2021-09-13 SBC: BOM
2021-09-16 SBC Controller: Add schematic and PCB
2021-09-17 SBC NH OLED interposer: Add schedmatic and PCB
2021-09-17 Add schematic PDFs
2021-09-21 SBC Controller: Work-around a missing resistor (for the controller's LED).
2021-10-12 README.md: Polish BOMs and document v1.0 errata
2021-10-12 SBC NH OLED interposer: v1.0 cleanup, no functional changes
2021-10-12 SBC Controller: Fix v1.0 errata
2021-10-12 SBC: Fix v1.0 errata
2021-10-12 Regenerate schematic PDFs
2021-10-12 Add a Kicad symbol for a tactile push button switch
2021-10-12 README.md: Update BOM for v1.1
2021-10-14 external/65xx: Create a local copy of the 65xx KiCad symbol library
    Preparatory step, prior to fixing the electrical type of the VIA and PIA GND pins.
    Copied pertinent files from https://github.com/mkeller0815/65xx_Library.
2021-10-14 external/65xx: Fix the electrical type of the VIA and PIA GND pins
    Output -> Power Input
2021-11-28 SBC v2.0
    Changes:
    - Second VIA
    - NMI button (hardware debounced)
    - 5 status LEDs (power and each VIA port)
    - Ground and power planes
    - Smaller footprint RAM and oscillator
2021-12-27 SBC USB Serial
2022-01-14 SBC v2.1
    Address some v2.0 errata:
    - SBC: Fix LED array layout
    - OLED interposer: Tidy silkscreen
2022-03-05 KiCad 6 symbols and footprints
2022-03-27 PLD: Add a description of the SBC v0 address decode logic
2022-04-25 SBC v2.2
    Changes over v2:
    - Address space decode and IRQ glue logic moved into a PLD
    - Adds serial port and power via USB-C connector
    - Adds onboard microSD mass storage
2022-07-22 SBC v2.3
    Fixes over v2.2:
    - SBC: Fix the VIA footprint: CA1 and CB1 are inputs
    - SBC: Move the microSD power enable line from (VIA3) CA1 (input) to CA2 (output)
    - Controller: connect LED enable
    - Controller: SMT switches
2023-04-19 SBC v2.3
    Fixes over v2.2:
    - SBC: Fix the VIA footprint: CA1 and CB1 are inputs
    - SBC: Move the microSD power enable line from (VIA3) CA1 (input) to CA2 (output)
    - SBC: Tie 65C02 SOB high
    - Controller: connect LED enable
    - Controller: SMT switches

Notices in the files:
sbc-exp-control/sbc-exp-control.kicad_pcb:
v2.3 | © 2022 Daniel Picken | https://github.com/dpicken/6502-hw
sbc-exp-erm4004_erm2004-interposer/sbc-exp-erm4004_erm2004-interposer.kicad_pcb:
v2.2 | © 2022 Daniel Picken | https://github.com/dpicken/6502-hw
sbc-exp-usb-serial/sbc-exp-usb-serial.kicad_pcb:
© 2021 Daniel Picken
